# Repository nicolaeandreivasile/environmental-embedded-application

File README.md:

# Environmental embedded device

####
An improved version of the AirSense wearable (obtained from a previous project), designed to collect and process environmental data as well as perform various tasks given the available functionalities.

####
Equipped with an ESP32 low-power high-performance microprocessor, two power sources, such as USB and a Li-Po battery, as well as a Li-Po charging module, environmental sensors and all the necessary modules for powering and programming the board, the embedded system is suitable for a wide variety of applications such as sensor networks, wearable devices and others

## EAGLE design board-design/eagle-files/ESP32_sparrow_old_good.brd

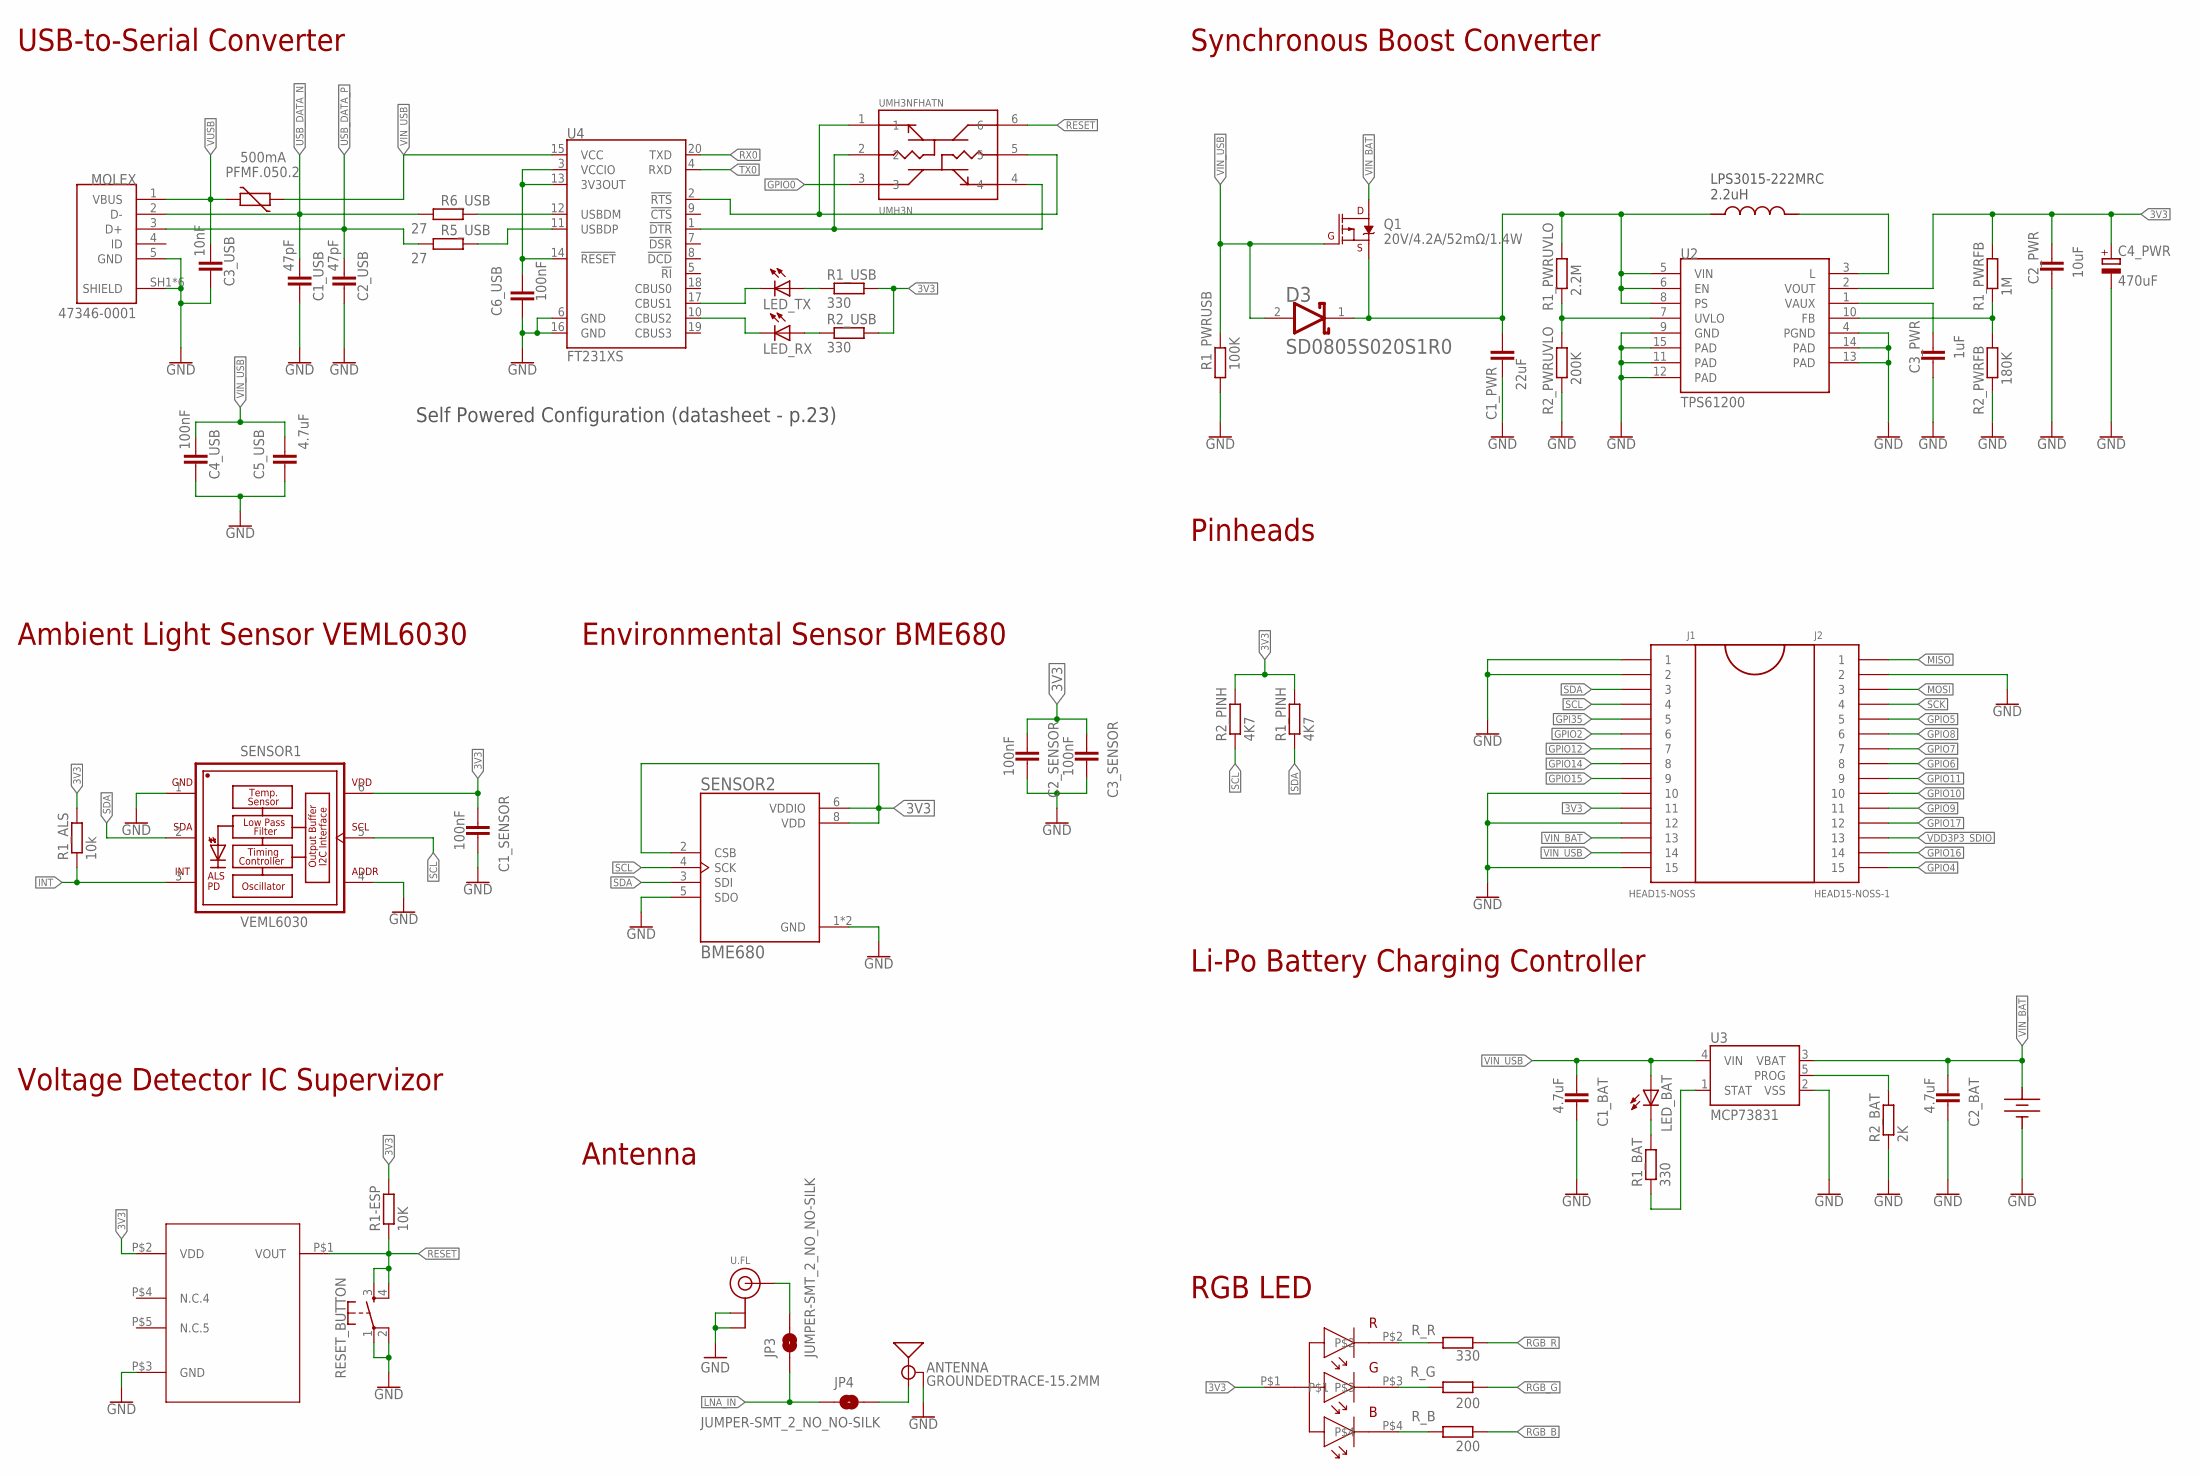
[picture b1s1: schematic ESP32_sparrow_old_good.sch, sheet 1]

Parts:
ANTENNA: GROUNDEDTRACE-15.2MM; TRACE_ANTENNA_2.4GHZ_15.2MM
C1_BAT, C2_BAT, C5_USB: 4.7uF; C0402
C1_PWR: 22uF; C0603
C1_SENSOR, C2_SENSOR, C3_SENSOR, C4_USB, C6_USB: 100nF; C0402
C1_USB, C2_USB: 47pF; C0402
C2_PWR: 10uF; C0402
C3_PWR: 1uF; C0402
C3_USB: 10nF; C0402
C4_PWR: 470uF; D/7343-31R
D3: AVX_SD0805S020S1R0AVX_SD0805S020S1R0_0_0; AVX_SD0805S020S1R0_0
J1: HEAD15-NOSS
J2: HEAD15-NOSS-1
JP3, JP4: JUMPER-SMT_2_NO_NO-SILK; SMT-JUMPER_2_NO_NO-SILK
LED_BAT: LEDCHIP-LED0603; CHIP-LED0603
LED_RX: LEDCHIP-LED0603; CHIP-LED0603
LED_TX: LEDCHIP-LED0603; CHIP-LED0603
MOLEX: 47346-0001; MOLEX_47346-0001
PFMF.050.2: 500mA; CT/CN1812
Q1: 20V/4.2A/52mΩ/1.4W; SOT23-3
R1-ESP: 10K; R0402
R1_ALS: 10k; R0402
R1_BAT, R1_USB, R2_USB: 330; R0402
R1_PINH, R2_PINH: 4K7; R0402
R1_PWRFB: 1M; R0402
R1_PWRUSB: 100K; R0402
R1_PWRUVLO: 2.2M; R0402
R2_BAT: 2K; R0402
R2_PWRFB: 180K; R0402
R2_PWRUVLO: 200K; R0402
R5_USB, R6_USB: 27; R0402
RESET_BUTTON: MOMENTARY-SWITCH-SPST-2-SMD-4.6X2.8MM; TACTILE_SWITCH_SMD_4.6X2.8MM
R_B: 200; R0402
R_G: 200; R0402
R_R: 330; R0402
SENSOR1: VEML6030; VISHAY_VEML6030_2X2X0.87
SENSOR2: BME680; PSON80P300X300X100-8N
U2: TPS61200; QFN-10_PAD
U3: MCP73831; SOT23-5
U4: FT231XS; SSOP20_L
U$1: 150202M153130-RGB; 150202M153130
U$2: BD48E27G-TR; SSOP5
U$4: 12BHC186CLP-GR
U$5: LPS3015; LPS3015-222MRC
U.FL: ANTENNA_U.FL; U.FL
UMH3NFHATN: UMH3NFHATN; SOP65P210X100-6N

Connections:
3V3: C1_SENSOR.2, C2_PWR.2, C2_SENSOR.2, C3_SENSOR.2, C4_PWR.+, J1.11, R1-ESP.2, R1_ALS.2, R1_PINH.2, R1_PWRFB.2, R1_USB.2, R2_PINH.2, R2_USB.2, SENSOR1.6 (VDD), SENSOR2.2 (CSB), SENSOR2.6 (VDDIO), SENSOR2.8 (VDD), U2.2 (VOUT), U$1.P$1, U$2.P$2 (VDD); also elsewhere on the board
GND: ANTENNA.GND, C1_BAT.1, C1_PWR.2, C1_SENSOR.1, C1_USB.2, C2_BAT.1, C2_PWR.1, C2_SENSOR.1, C2_USB.2, C3_PWR.1, C3_SENSOR.1, C3_USB.2, C4_PWR.-, C4_USB.2, C5_USB.2, C6_USB.2, J1.1, J1.2, J1.10, J1.12, J1.15, J2.2, MOLEX.5 (GND), MOLEX.SH1 (SHIELD), MOLEX.SH2 (SHIELD), MOLEX.SH3 (SHIELD), MOLEX.SH4 (SHIELD), MOLEX.SH5 (SHIELD), MOLEX.SH6 (SHIELD), R1_PWRUSB.1, R2_BAT.1, R2_PWRFB.1, R2_PWRUVLO.1, RESET_BUTTON.1, RESET_BUTTON.2, SENSOR1.1 (GND), SENSOR1.4 (ADDR), SENSOR2.1 (GND), SENSOR2.5 (SDO), SENSOR2.7 (GND), U2.4 (PGND), U2.9 (GND), U2.11 (PAD), U2.12 (PAD), U2.13 (PAD), U2.14 (PAD), U2.15 (PAD), U3.2 (VSS), U4.6 (GND), U4.16 (GND), U$2.P$3 (GND), U$4.P$1 (G), U$4.P$3 (G), U$4.P$4 (G), U.FL.1 (GND), U.FL.2 (GND); also elsewhere on the board
GPI35: J1.5; also elsewhere on the board
GPIO0: UMH3NFHATN.3; also elsewhere on the board
GPIO2: J1.6; also elsewhere on the board
GPIO4: J2.15; also elsewhere on the board
GPIO5: J2.5; also elsewhere on the board
GPIO6: J2.8; also elsewhere on the board
GPIO7: J2.7; also elsewhere on the board
GPIO8: J2.6; also elsewhere on the board
GPIO9: J2.11; also elsewhere on the board
GPIO10: J2.10; also elsewhere on the board
GPIO11: J2.9; also elsewhere on the board
GPIO12: J1.7; also elsewhere on the board
GPIO14: J1.8; also elsewhere on the board
GPIO15: J1.9; also elsewhere on the board
GPIO16: J2.14; also elsewhere on the board
GPIO17: J2.12; also elsewhere on the board
INT: R1_ALS.1, SENSOR1.3 (INT); also elsewhere on the board
LNA_IN: JP3.1, JP4.1; also elsewhere on the board
MISO: J2.1; also elsewhere on the board
MOSI: J2.3; also elsewhere on the board
unnamed: R1_PWRFB.1, R2_PWRFB.2, U2.10 (FB)
unnamed: R_B.2, U$1.P$4
unnamed: R_G.2, U$1.P$3
unnamed: R_R.2, U$1.P$2
unnamed: U4.1 (!DTR), UMH3NFHATN.2, UMH3NFHATN.4
unnamed: U4.2 (!RTS), UMH3NFHATN.1, UMH3NFHATN.5
unnamed: ANTENNA.ANT (SIGNAL), JP4.2
unnamed: C6_USB.1, U4.3 (VCCIO), U4.13 (3V3OUT), U4.14 (!RESET)
unnamed: R1_PWRUVLO.1, R2_PWRUVLO.2, U2.7 (UVLO)
unnamed: U2.3 (L), U$5.P$2
unnamed: LED_BAT.C, R1_BAT.2
unnamed: R1_BAT.1, U3.1 (STAT)
unnamed: LED_TX.C, U4.17 (CBUS1)
unnamed: JP3.2, U.FL.3 (SIGNAL)
unnamed: C3_PWR.2, U2.1 (VAUX)
unnamed: R6_USB.2, U4.12 (USBDM)
unnamed: LED_TX.A, R1_USB.1
unnamed: LED_RX.C, U4.10 (CBUS2)
unnamed: LED_RX.A, R2_USB.1
unnamed: R5_USB.2, U4.11 (USBDP)
unnamed: R2_BAT.2, U3.5 (PROG)
RESET: R1-ESP.1, RESET_BUTTON.3, RESET_BUTTON.4, U$2.P$1 (VOUT), UMH3NFHATN.6; also elsewhere on the board
RGB_B: R_B.1; also elsewhere on the board
RGB_G: R_G.1; also elsewhere on the board
RGB_R: R_R.1; also elsewhere on the board
RX0: U4.20 (TXD); also elsewhere on the board
SCK: J2.4; also elsewhere on the board
SCL: J1.4, R2_PINH.1, SENSOR1.5 (SCL), SENSOR2.4 (SCK); also elsewhere on the board
SDA: J1.3, R1_PINH.1, SENSOR1.2 (SDA), SENSOR2.3 (SDI); also elsewhere on the board
TX0: U4.4 (RXD); also elsewhere on the board
USB_DATA_N: C1_USB.1, MOLEX.2 (D-), R6_USB.1
USB_DATA_P: C2_USB.1, MOLEX.3 (D+), R5_USB.1
VDD3P3_SDIO: J2.13; also elsewhere on the board
VIN: C1_PWR.1, D3.1 (CATHODE), Q1.2 (S), R1_PWRUVLO.2, U2.5 (VIN), U2.6 (EN), U2.8 (PS), U$5.P$1
VIN_BAT: C2_BAT.2, J1.13, Q1.3 (D), U3.3 (VBAT), U$4.P$2, U$4.P$5, U$4.P$6; also elsewhere on the board
VIN_USB: C1_BAT.2, C4_USB.1, C5_USB.1, D3.2 (ANODE), J1.14, LED_BAT.A, PFMF.050.2.1, Q1.1 (G), R1_PWRUSB.2, U3.4 (VIN), U4.15 (VCC)
VUSB: C3_USB.1, MOLEX.1 (VBUS), PFMF.050.2.2

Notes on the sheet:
Self Powered Configuration (datasheet - p.23)
RGB LED
USB-to-Serial Converter
Synchronous Boost Converter
Pinheads
Environmental Sensor BME680
Ambient Light Sensor VEML6030
Voltage Detector IC Supervizor
Antenna
Li-Po Battery Charging Controller

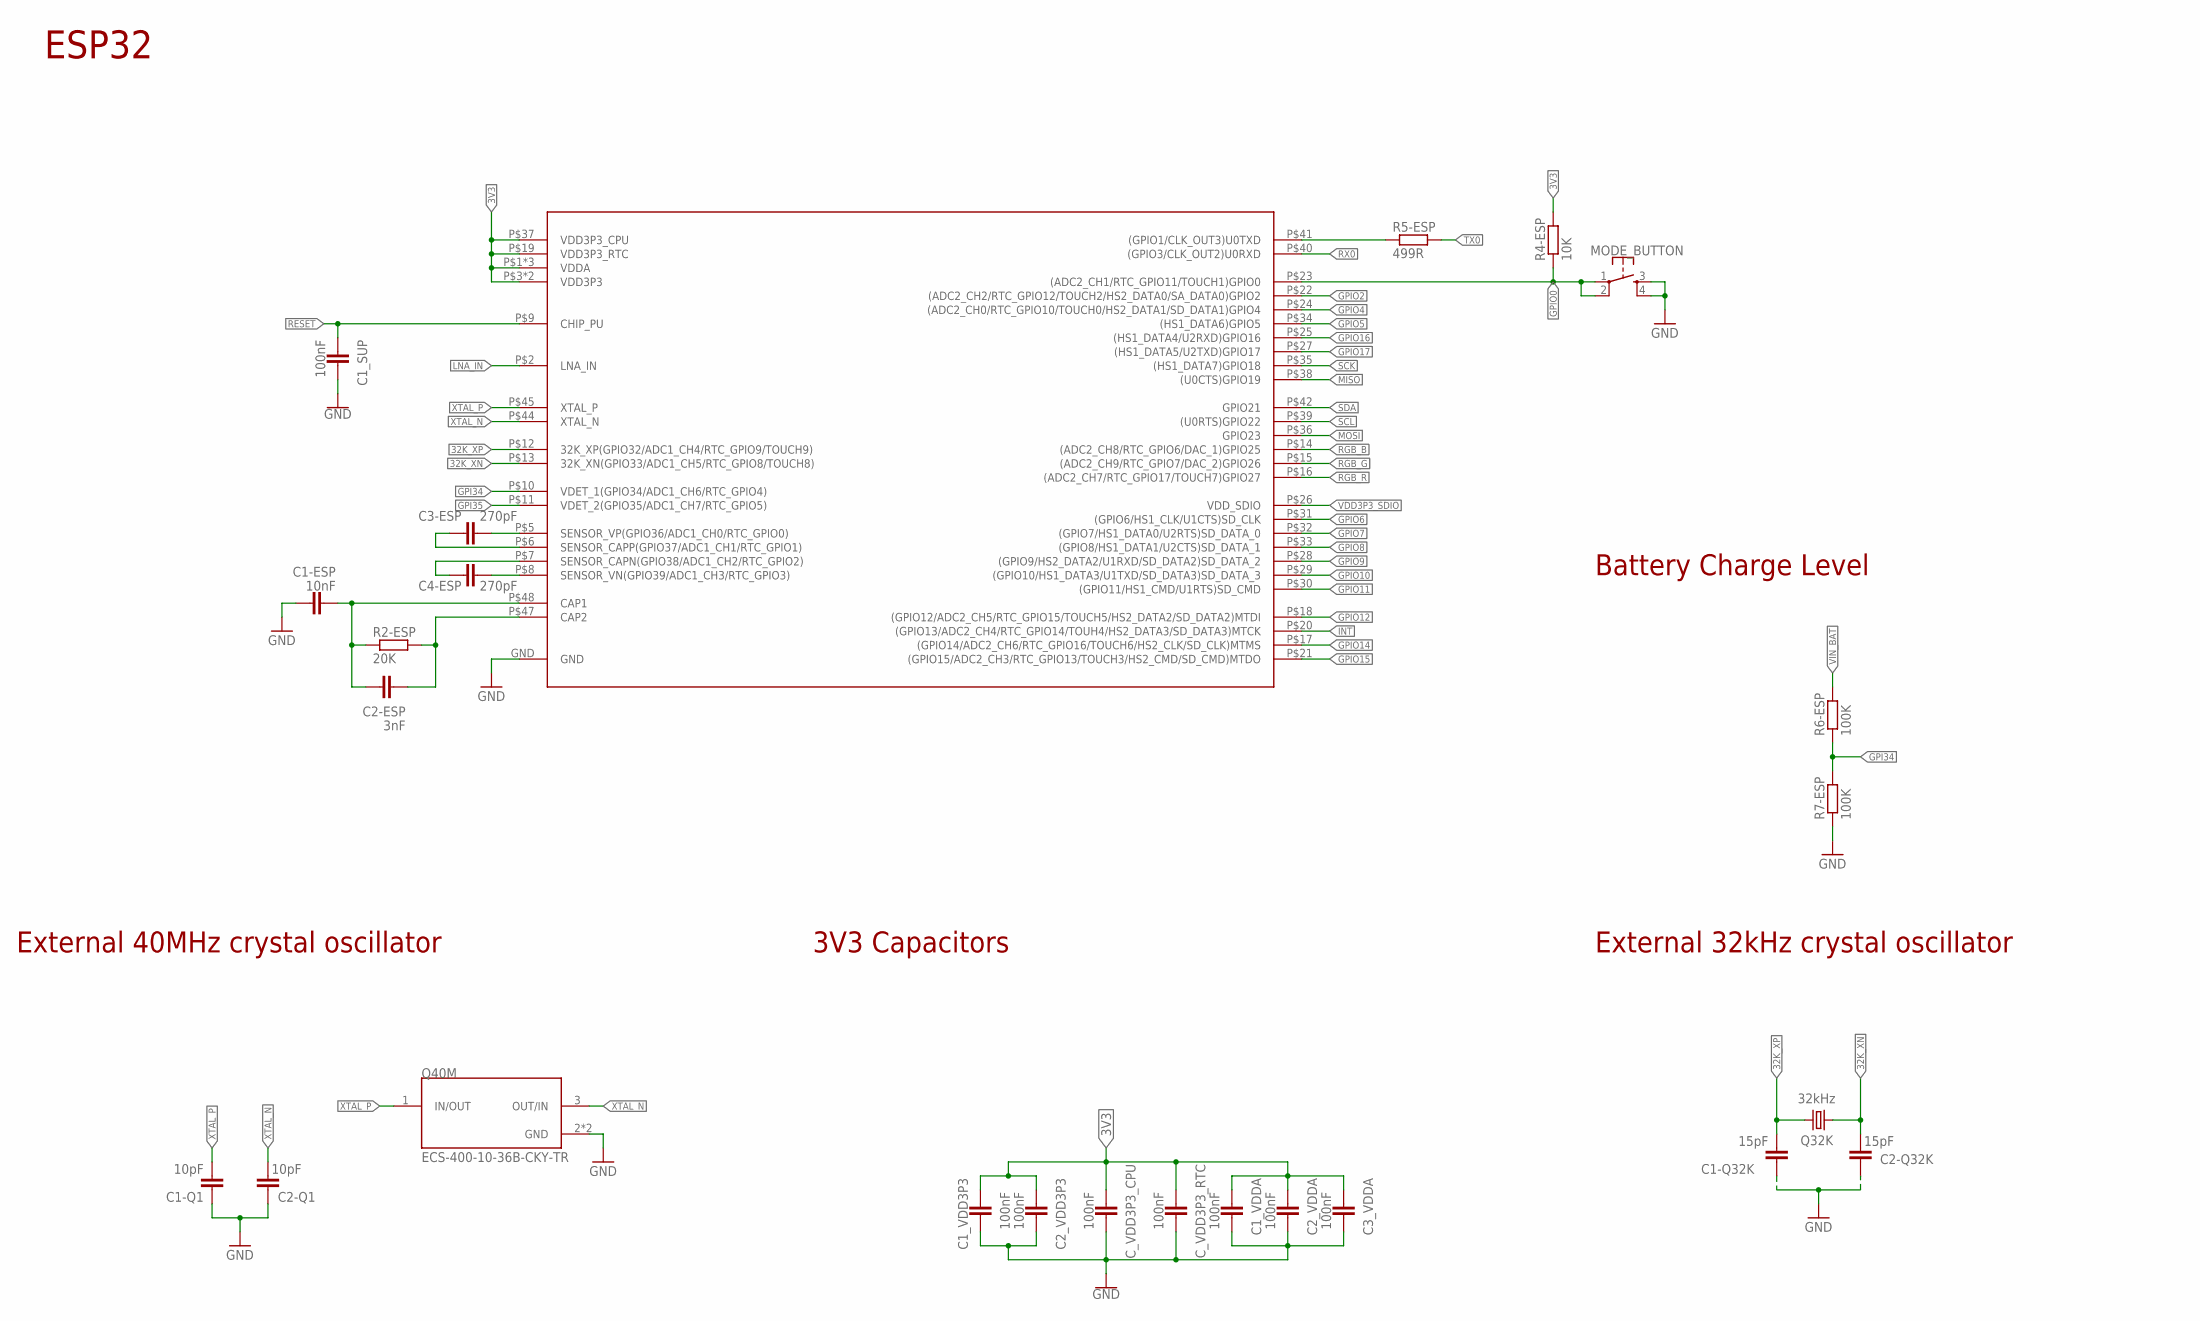
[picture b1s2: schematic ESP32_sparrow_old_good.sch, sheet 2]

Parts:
C1-ESP: 10nF; C0402
C1-Q1, C2-Q1: 10pF; C0402
C1-Q32K, C2-Q32K: 15pF; C0402
C1_SUP, C1_VDD3P3, C1_VDDA, C2_VDD3P3, C2_VDDA, C3_VDDA: 100nF; C0402
C2-ESP: 3nF; C0402
C3-ESP, C4-ESP: 270pF; C0402
C_VDD3P3_CPU, C_VDD3P3_RTC: 100nF; C0402
MODE_BUTTON: MOMENTARY-SWITCH-SPST-2-SMD-4.6X2.8MM; TACTILE_SWITCH_SMD_4.6X2.8MM
Q32K: 32kHz; FC-12M
Q40M: ECS-400-10-36B-CKY-TR; XTAL_ECS-163.84-10-36-JGN-TR
R2-ESP: 20K; R0402
R4-ESP: 10K; R0402
R5-ESP: 499R; R0402
R6-ESP, R7-ESP: 100K; R0402
U$3: ESP32-U4WDH

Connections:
3V3: C1_VDD3P3.2, C1_VDDA.2, C2_VDD3P3.2, C2_VDDA.2, C3_VDDA.2, C_VDD3P3_CPU.2, C_VDD3P3_RTC.2, R4-ESP.2, U$3.P$1 (VDDA), U$3.P$3 (VDD3P3), U$3.P$4 (VDD3P3), U$3.P$19 (VDD3P3_RTC), U$3.P$37 (VDD3P3_CPU), U$3.P$43 (VDDA), U$3.P$46 (VDDA); also elsewhere on the board
32K_XN: C2-Q32K.2, Q32K.1, U$3.P$13 (32K_XN(GPIO33/ADC1_CH5/RTC_GPIO8/TOUCH8))
32K_XP: C1-Q32K.2, Q32K.2, U$3.P$12 (32K_XP(GPIO32/ADC1_CH4/RTC_GPIO9/TOUCH9))
GND: C1-ESP.1, C1-Q1.1, C1-Q32K.1, C1_SUP.1, C1_VDD3P3.1, C1_VDDA.1, C2-Q1.1, C2-Q32K.1, C2_VDD3P3.1, C2_VDDA.1, C3_VDDA.1, C_VDD3P3_CPU.1, C_VDD3P3_RTC.1, MODE_BUTTON.3, MODE_BUTTON.4, Q40M.2 (GND), Q40M.4 (GND), R7-ESP.1, U$3.GND; also elsewhere on the board
GPI34: R6-ESP.1, R7-ESP.2, U$3.P$10 (VDET_1(GPIO34/ADC1_CH6/RTC_GPIO4))
GPI35: U$3.P$11 (VDET_2(GPIO35/ADC1_CH7/RTC_GPIO5)); also elsewhere on the board
GPIO0: MODE_BUTTON.1, MODE_BUTTON.2, R4-ESP.1, U$3.P$23 ((ADC2_CH1/RTC_GPIO11/TOUCH1)GPIO0); also elsewhere on the board
GPIO2: U$3.P$22 ((ADC2_CH2/RTC_GPIO12/TOUCH2/HS2_DATA0/S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); also elsewhere on the board
GPIO4: U$3.P$24 ((ADC2_CH0/RTC_GPIO10/TOUCH0/HS2_DATA1/S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); also elsewhere on the board
GPIO5: U$3.P$34 ((HS1_DATA6)GPIO5); also elsewhere on the board
GPIO6: U$3.P$31 ((GPIO6/HS1_CLK/U1CTS)SD_CLK); also elsewhere on the board
GPIO7: U$3.P$32 ((GPIO7/HS1_DATA0/U2RTS)SD_DATA_0); also elsewhere on the board
GPIO8: U$3.P$33 ((GPIO8/HS1_DATA1/U2CTS)SD_DATA_1); also elsewhere on the board
GPIO9: U$3.P$28 ((GPIO9/HS2_DATA2/U1RXD/SD_DATA2)SD_DATA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); also elsewhere on the board
GPIO10: U$3.P$29 ((GPIO10/HS1_DATA3/U1TXD/SD_DATA3)SD_DAT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); also elsewhere on the board
GPIO11: U$3.P$30 ((GPIO11/HS1_CMD/U1RTS)SD_CMD); also elsewhere on the board
GPIO12: U$3.P$18 ((GPIO12/ADC2_CH5/RTC_GPIO15/TOUCH5/HS2_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); also elsewhere on the board
GPIO14: U$3.P$17 ((GPIO14/ADC2_CH6/RTC_GPIO16/TOUCH6/HS2_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); also elsewhere on the board
GPIO15: U$3.P$21 ((GPIO15/ADC2_CH3/RTC_GPIO13/TOUCH3/HS2_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); also elsewhere on the board
GPIO16: U$3.P$25 ((HS1_DATA4/U2RXD)GPIO16); also elsewhere on the board
GPIO17: U$3.P$27 ((HS1_DATA5/U2TXD)GPIO17); also elsewhere on the board
INT: U$3.P$20 ((GPIO13/ADC2_CH4/RTC_GPIO14/TOUH4/HS2_D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); also elsewhere on the board
LNA_IN: U$3.P$2 (LNA_IN); also elsewhere on the board
MISO: U$3.P$38 ((U0CTS)GPIO19); also elsewhere on the board
MOSI: U$3.P$36 (GPIO23); also elsewhere on the board
unnamed: R5-ESP.1, U$3.P$41 ((GPIO1/CLK_OUT3)U0TXD)
unnamed: C1-ESP.2, C2-ESP.1, R2-ESP.1, U$3.P$48 (CAP1)
unnamed: C2-ESP.2, R2-ESP.2, U$3.P$47 (CAP2)
unnamed: C3-ESP.1, U$3.P$6 (SENSOR_CAPP(GPIO37/ADC1_CH1/RTC_GPIO1))
unnamed: C3-ESP.2, U$3.P$5 (SENSOR_VP(GPIO36/ADC1_CH0/RTC_GPIO0))
unnamed: C4-ESP.1, U$3.P$7 (SENSOR_CAPN(GPIO38/ADC1_CH2/RTC_GPIO2))
unnamed: C4-ESP.2, U$3.P$8 (SENSOR_VN(GPIO39/ADC1_CH3/RTC_GPIO3))
RESET: C1_SUP.2, U$3.P$9 (CHIP_PU); also elsewhere on the board
RGB_B: U$3.P$14 ((ADC2_CH8/RTC_GPIO6/DAC_1)GPIO25); also elsewhere on the board
RGB_G: U$3.P$15 ((ADC2_CH9/RTC_GPIO7/DAC_2)GPIO26); also elsewhere on the board
RGB_R: U$3.P$16 ((ADC2_CH7/RTC_GPIO17/TOUCH7)GPIO27); also elsewhere on the board
RX0: U$3.P$40 ((GPIO3/CLK_OUT2)U0RXD); also elsewhere on the board
SCK: U$3.P$35 ((HS1_DATA7)GPIO18); also elsewhere on the board
SCL: U$3.P$39 ((U0RTS)GPIO22); also elsewhere on the board
SDA: U$3.P$42 (GPIO21); also elsewhere on the board
TX0: R5-ESP.2; also elsewhere on the board
VDD3P3_SDIO: U$3.P$26 (VDD_SDIO); also elsewhere on the board
VIN_BAT: R6-ESP.2; also elsewhere on the board
XTAL_N: C2-Q1.2, Q40M.3 (OUT/IN), U$3.P$44 (XTAL_N)
XTAL_P: C1-Q1.2, Q40M.1 (IN/OUT), U$3.P$45 (XTAL_P)

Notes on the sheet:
ESP32
External 40MHz crystal oscillator
3V3 Capacitors
External 32kHz crystal oscillator
Battery Charge Level

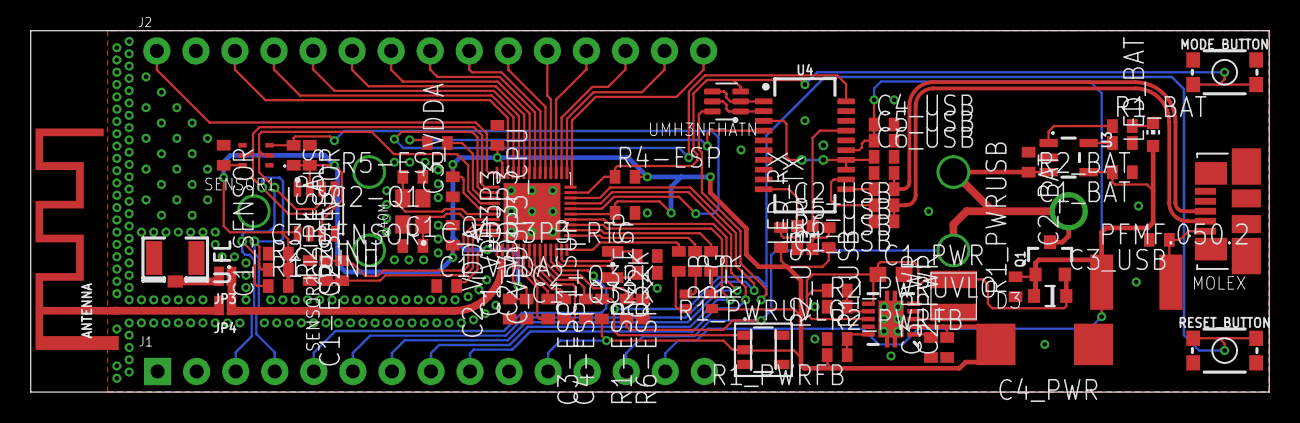
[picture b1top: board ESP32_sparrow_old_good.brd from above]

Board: 2 copper layers, 80.5 x 23.5 mm, 82 parts (0 on the bottom side), 71 nets.

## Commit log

2021-10-17 Initial files added

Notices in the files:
parts and their libraries:
SparkFun-RF: Licensing: Creative Commons ShareAlike 4.0 International - https://creativecommons.org/licenses/by-sa/4.0
